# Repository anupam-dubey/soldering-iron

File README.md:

# Temperature Cnntrolled soldering iron
</br> 

## Description
USES popular nano mega328P ,The device controlles Temperature of  soldering iron based on hakko 907 models with inbuilt temperature sensor
Four Wires used in soldering iron contains heater and thermocouple sensor, heater wire is connected to arduino pin 11 for pwm via popular IRF44 mosfet
sensor wire goes to LM358 opamp for gain of 45 first stage and 2 for second stage gives a total gain of 90. It is adviced that before makeing this project be sure about thermocouple and heater wires and check the thermocouple using multimeter for determination of gain value. 
To calibrate the soldering station I use an external thermocouple with a multimeter that can measure temperatures. 
(Although other devices could be used)
The procedure consists of the following steps.
1. Rotate the soldering station's encoder to set a temperature value. Wait until the actual temperature stabilizes (the actual temperature = the set temperature). Let Xi be the set temperature.
2. Using an external thermocouple measure the temperature of the soldering iron's tip. Let Yi be the temperature measured by an external device.
3. Using different set temperatures repeat 1-2 steps a few times . i=1,2,...n
4. Now we have the set of points (X1,Y1),(X2,Y2),....,(Xn,Yn)
5. Find a function that maps Xi to Yi for all i=1,..,n.
If we have only 2 points (X1,Y1),(X2,Y2), then we can draw the line (Y=a*X+b) between the points. This line will be the solution to the problem.  If we have more than 2 points, we should use the method of least squares.
6. Use the function to convert ADC's numbers to actual temperatures.

|No |	Xi set temperature	|Yi temperature measured by an external device|
|---|	------------------	|---------|
|1	|40                 	|52|
|2	|80	                    |95|
|3	|100                    |125|
|4	|160	                |195|

We can use an online service to find the function.
Let's open wolframalpha.com. Then we should type the string "linear fit {40,52},{80,95},{100,125},{160,195}" in the edit box.
The solution for our problem is y= 1.202 x+2.56.
I used this function in the arduino's sketch to convert ADC's numbers to actual
temperatures.

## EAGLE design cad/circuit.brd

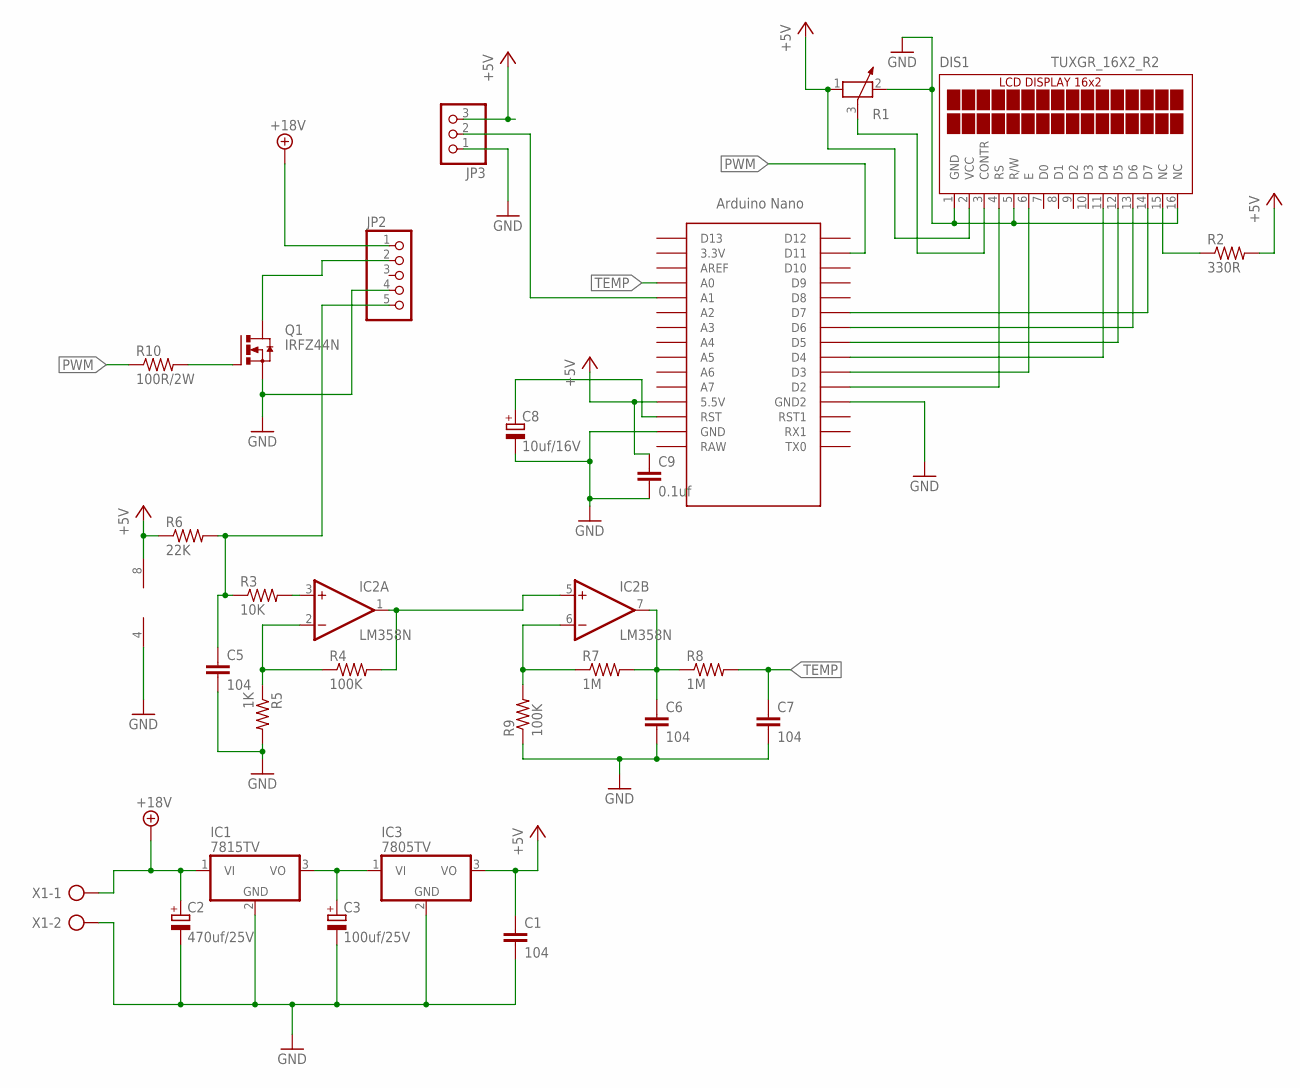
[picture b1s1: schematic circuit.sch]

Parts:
C1, C5, C6, C7: 104; C025-025X050
C2: 470uf/25V; E2,5-7
C3: 100uf/25V; E2,5-6
C8: 10uf/16V; E2-5
C9: 0.1uf; C025-040X050
DIS1: TUXGR_16X2_R2
IC1: 7815TV; TO220V
IC2: LM358N; DIL08
IC3: 7805TV; TO220V
JP2: PINHD-1X5; 1X05
JP3: PINHD-1X3; 1X03
Q1: IRFZ44N; TO220BV
R1: POTENTIOMETER_PT-10; PT-10
R2: 330R; 0207/10
R3: 10K; 0207/10
R4, R9: 100K; 0207/10
R5: 1K; 0207/10
R6: 22K; 0207/10
R7, R8: 1M; 0207/10
R10: 100R/2W; 0411/15
U$2: NANO
X1: AK500/2

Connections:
+5V: C1.1, C9.1, DIS1.2 (VCC), IC2.8 (V+), IC3.3 (VO), JP3.3, R1.1, R2.2, R6.1, U$2.5V (5.5V)
+18V: C2.+, IC1.1 (VI), JP2.1, X1.1
GND: C1.2, C2.-, C3.-, C5.2, C6.2, C7.2, C8.-, C9.2, DIS1.1 (GND), DIS1.5 (R/W), DIS1.16 (NC), IC1.2 (GND), IC2.4 (V-), IC3.2 (GND), JP2.4, JP3.1, Q1.S, R1.2, R5.2, R9.1, U$2.GND, U$2.GND1 (GND2), X1.2
unnamed: JP2.2, Q1.D
unnamed: IC2.1 (OUT), IC2.5 (+IN), R4.2
unnamed: C3.+, IC1.3 (VO), IC3.1 (VI)
unnamed: IC2.2 (-IN), R4.1, R5.1
unnamed: IC2.3 (+IN), R3.2
unnamed: DIS1.4 (RS), U$2.D2
unnamed: C5.1, JP2.5, R3.1, R6.2
unnamed: JP3.2, U$2.A1
unnamed: IC2.6 (-IN), R7.1, R9.2
unnamed: C6.1, IC2.7 (OUT), R7.2, R8.1
unnamed: Q1.G, R10.2
unnamed: DIS1.6 (E), U$2.D3
unnamed: C8.+, U$2.RST
unnamed: DIS1.11 (D4), U$2.D4
unnamed: DIS1.12 (D5), U$2.D5
unnamed: DIS1.13 (D6), U$2.D6
unnamed: DIS1.14 (D7), U$2.D7
unnamed: DIS1.3 (CONTR), R1.3
unnamed: DIS1.15 (NC), R2.1
PWM: R10.1, U$2.D11
TEMP: C7.1, R8.2, U$2.A0

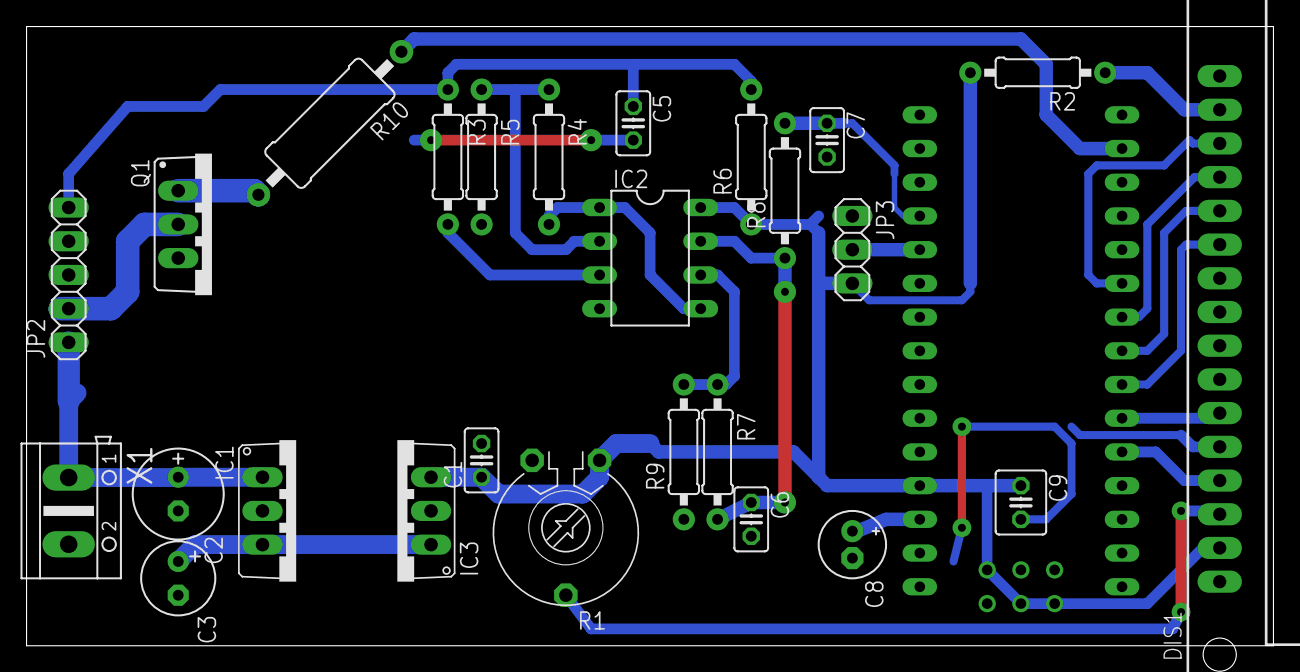
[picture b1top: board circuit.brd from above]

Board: 2 copper layers, 94.0 x 46.7 mm, 27 parts (0 on the bottom side), 24 nets.
